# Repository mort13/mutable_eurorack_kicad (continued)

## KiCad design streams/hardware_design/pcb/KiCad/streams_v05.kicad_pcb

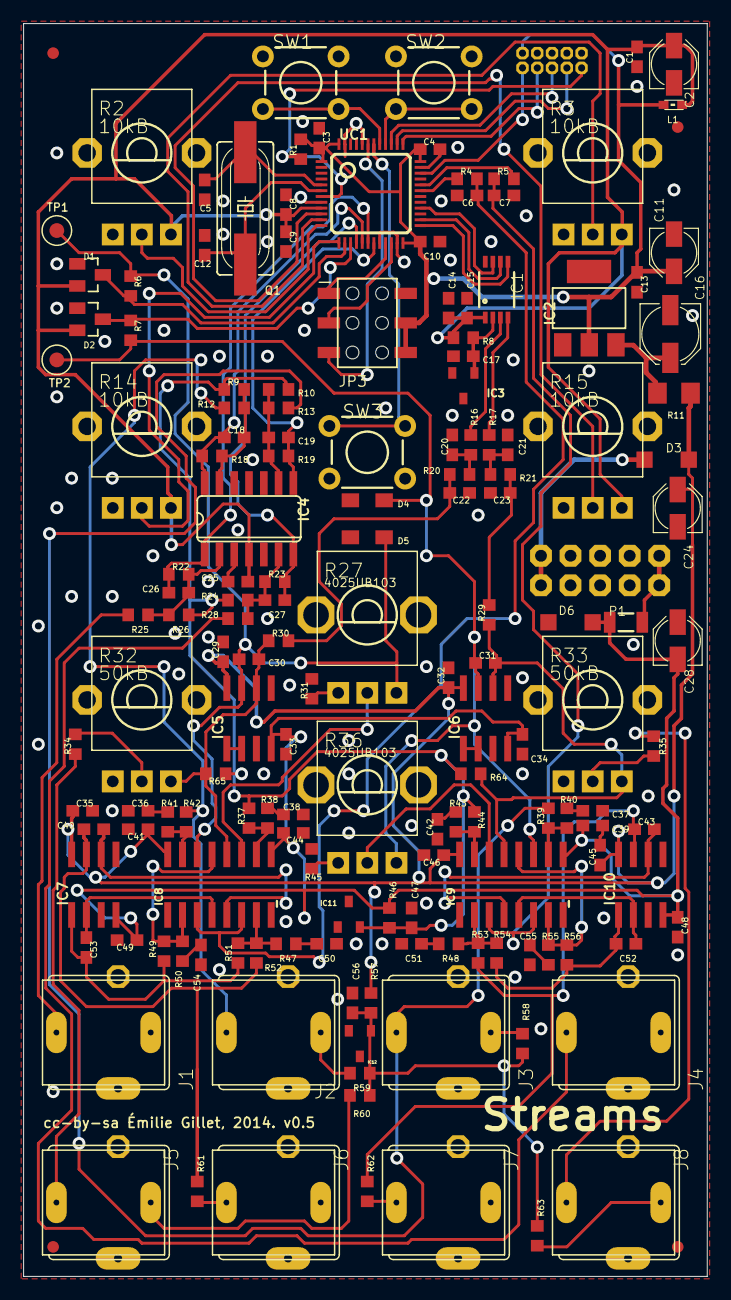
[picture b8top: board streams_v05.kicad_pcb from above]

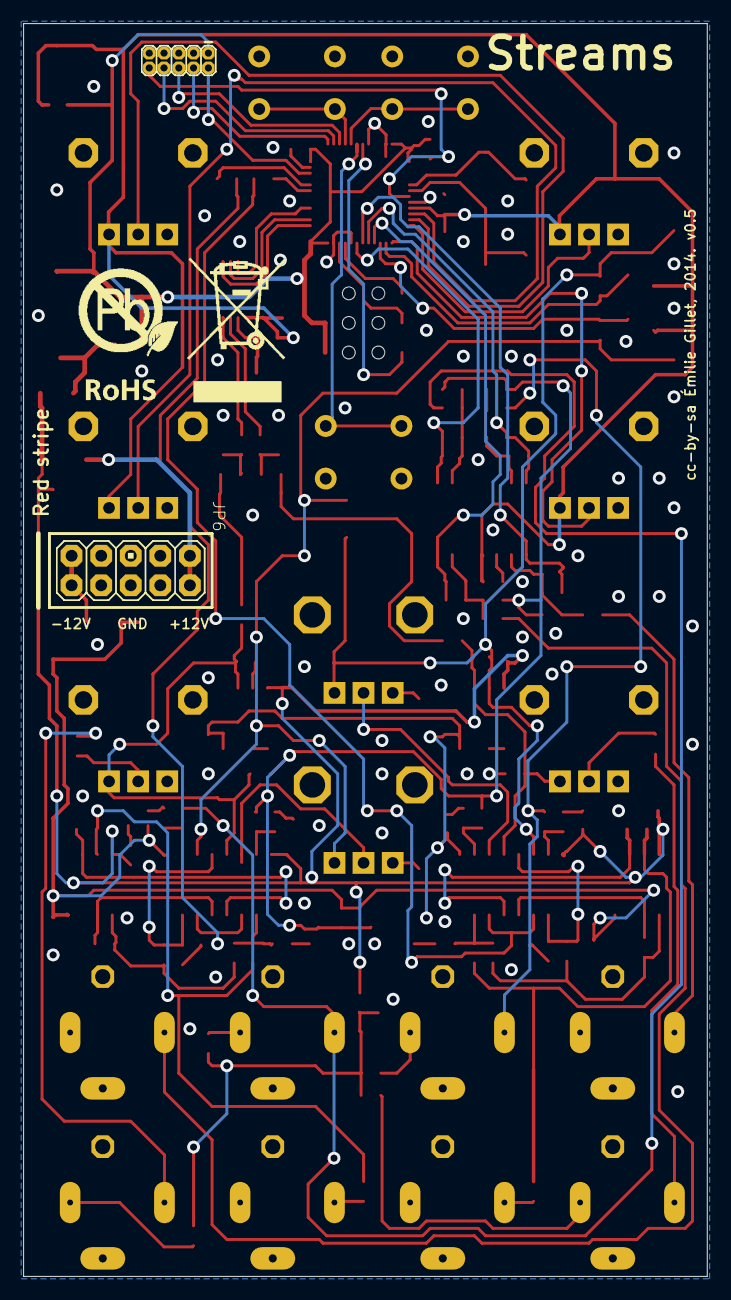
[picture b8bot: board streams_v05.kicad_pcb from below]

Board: 2 copper layers, 58.7 x 107.6 mm, 164 parts (3 on the bottom side), 99 nets.

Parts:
C1, C3, C4, C8, C10, C13, C14, C17, C25, C29, C32, C33, C34, C35, C39, C41, C44, C45, C46, C47, C48, C49, C56: 100n; C0603
C2, C24, C28: 10u; PANASONIC_B
C5, C12: 18p; C0603
C6, C7: 680n; C0603
C9, C15: 3.3u; C0603
C11: 22u; PANASONIC_B
C16: 22u; PANASONIC_C
C18, C19, C22, C23, C26, C27: 1.0n; C0603
C20, C21: 10n; C0603
C30, C31, C40, C43, C52, C53: 33p; C0603
C36, C37, C38, C42, C50, C51, C54, C55: 560p; C0603
D1, D2: BAT54S; SOT23
D3, D6: 1N5819HW; SOD123
D4, D5: 1N4148; SOD323-W
IC1: DAC8552; MSOP-8
IC2: LM1117-3.3; SOT223
IC3: LM4040B25; DBZ_R-PDSO-G3
IC4: MCP6004; SO14
IC5, IC6, IC7, IC10: TL072D; SO08
IC8, IC9: V2164SZ; SOIC16N
IC11, IC12: LM4040B10; DBZ_R-PDSO-G3
J1, J2, J3, J4, J5, J6, J7, J8: PJ301WQP; WQP_PJ_301BM_WIDER
JP1, JP2, JP4, JP5: FIDUCIAL1X2; FIDUCIAL-1X2
JP3: 2X3_BOTTOM
JP6: M05X2PTH; AVR_ICSP
JP7: M05X2MINIJTAG; 2X5-1.27
L1: 0603
P1: PTCSMD; PTC-1206
Q1: 8MHz; HC49UP
R1, R20, R21: 10k; R0603
R2, R3, R14, R15: 10kB; ALPS_POT_VERTICAL_PS
R4, R5: 1.2k; R0603
R6, R7, R16, R17, R46, R61, R62: 1.0k; R0603
R8, R57: 3.3k; R0603
R9, R10, R24, R26: 120k; R0603
R11: 4.7; R1206
R12, R13, R25, R28, R34, R35, R39, R42, R49, R51, R52, R53, R54, R56, R58, R59: 100k; R0603
R18, R19, R22, R23: 20k; R0603
R27, R36: 4025UB103; ALPS_POT_VERTICAL
R29, R30: 14k; R0603
R31, R38, R40, R41, R43, R45, R47, R48, R50, R55: 510; R0603
R32, R33: 50kB; ALPS_POT_VERTICAL_PS
R37, R44: 200k; R0603
R60, R63: 24.9k; R0603
R64, R65: 10M; R0603
SW1, SW2, SW3: TACTILE-PTH
TP1, TP2: TEST-POINT3X5; PAD.03X.05
U$1: ROHS_BIG
UC1: STM32F103CBT6; LQFP48

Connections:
+3V3: C3.1, C4.1, C10.1, C11.+, C13.1, IC2.2, JP3.4, JP3.6, JP7.1, L1.1, R1.2, UC1.1, UC1.24, UC1.36, UC1.48
+3V3_A: C1.1, C2.+, C8.1, C9.1, C14.1, C15.1, C25.1, D1.2, D2.2, IC1.1, IC4.4, L1.2, R2.P$1, R3.P$1, R8.1, R14.P$1, R15.P$1, UC1.9
ADC_AUX_1: C26.2, IC4.1, R22.2, UC1.18
ADC_AUX_2: C27.2, IC4.7, R23.2, UC1.16
ADC_CV_1: D1.3, R6.1, UC1.14
ADC_CV_2: D2.3, R7.1, UC1.15
ADC_IN_1: C18.2, IC4.14, R18.2, UC1.17
ADC_IN_2: C19.2, IC4.8, R19.2, UC1.19
AMOUNT_1: R14.P$2, UC1.13
AMOUNT_2: R15.P$2, UC1.10
AREF_2.5: C17.1, IC1.2, IC3.1, R8.2
AREF_+5: J2.SW, R59.1
AREF_+10: C56.1, IC12.1, R57.2, R58.2, R59.2, R60.2, R63.2
AREF_-10: C47.1, IC11.2, R9.1, R10.1, R24.1, R26.1, R37.1, R44.1, R46.2, R64.1, R65.1
BARGRAPH_CS: JP3.5, UC1.43
BARGRAPH_MOSI: JP3.1, UC1.21
BARGRAPH_SCK: JP3.3, UC1.22
DAC_1: C22.1, R20.2, R30.1
DAC_2: C23.1, R21.2, R29.1
DAC_MOSI: IC1.7, UC1.28
DAC_SCK: IC1.6, UC1.26
DAC_SS: IC1.5, UC1.25
FB_CURRENT1: IC8.10, R37.2, R38.2
FB_CURRENT2: IC8.15, R41.2, R42.2
FB_CURRENT3: IC9.10, R39.2, R40.2
FB_CURRENT4: IC9.15, R43.2, R44.2
GND: C1.2, C2.-, C3.2, C4.2, C5.1, C6.2, C7.2, C8.2, C9.2, C10.2, C11.-, C12.1, C13.2, C14.2, C15.2, C16.-, C17.2, C20.2, C21.2, C22.2, C23.2, C24.-, C25.2, C28.+, C29.2, C32.2, C33.1, C34.1, C35.2, C36.2, C37.2, C38.2, C39.1, C41.2, C42.2, C44.1, C45.2, C46.2, C47.2, C48.1, C49.1, C50.2, C51.2, C54.2, C55.2, C56.2, D1.1, D2.1, D4.A, D5.A, D6.C, IC1.8, IC2.1, IC3.2, IC4.3, IC4.5, IC4.10, IC4.11, IC4.12, IC5.3, IC5.5, IC6.3, IC6.5, IC7.3, IC7.5, IC8.8, IC9.8, IC10.3, IC10.5, IC11.1, IC12.2, J1.GND, J1.GND2, J2.GND, J2.GND2, J3.GND, J3.GND2, J4.GND, J4.GND2, J5.GND, J5.GND2, J6.GND, J6.GND2, J7.GND, J7.GND2, J8.GND, J8.GND2, JP3.2, JP6.3, JP6.4, JP6.5, JP6.6, JP6.7, JP6.8, JP7.3, JP7.5, JP7.9, R2.P$3, R3.P$3, R14.P$3, R15.P$3, R31.1, R32.P$3, R33.P$3, R45.1, SW1.1, SW1.2, SW2.1, SW2.2, SW3.1, SW3.2, UC1.8, UC1.20, UC1.23, UC1.35, UC1.44, UC1.47
IN_1: J2.TIP, R12.1, R42.1
IN_2: J3.TIP, R13.1, R39.1
JTCK: JP7.4, UC1.37
JTDI: JP7.8, UC1.38
JTDO: JP7.6, UC1.39
JTMS: JP7.2, UC1.34
unnamed: R27.P$3, R31.2
unnamed: C30.1, IC5.6, IC8.12, R30.2, R32.P$1, R65.2
unnamed: J8.SW, R63.1
unnamed: C37.1, R40.1
unnamed: C38.1, R38.1
unnamed: C5.2, Q1.2, UC1.5
unnamed: C12.2, Q1.1, UC1.6
unnamed: C31.1, IC6.6, IC9.13, R29.2, R33.P$1, R64.2
unnamed: C36.1, R41.1
unnamed: IC5.1, IC5.2
unnamed: J5.SW, R60.1
unnamed: J5.TIP, R34.1
unnamed: C43.1, IC9.4, IC10.6
unnamed: IC8.11, R27.P$2
unnamed: C43.2, IC10.7, R53.2, R62.1
unnamed: J7.TIP, R62.2
unnamed: R36.P$3, R45.2
unnamed: C42.1, R43.1
unnamed: C16.+, IC2.3, R11.2
unnamed: R32.P$2, R34.2
unnamed: R33.P$2, R35.2
unnamed: J8.TIP, R35.1
unnamed: C40.1, IC7.6, IC8.5
unnamed: C40.2, IC7.7, R52.2, R61.1
unnamed: IC6.1, IC6.2
unnamed: IC9.14, R36.P$2
unnamed: J3.SW, R58.1
unnamed: IC8.2, IC8.13, R49.1, R50.2
unnamed: D3.A, JP6.1, JP6.2
unnamed: JP6.9, JP6.10, P1.2
unnamed: J1.TIP, R25.1
unnamed: C27.1, IC4.6, R23.1, R24.2, R28.2
unnamed: J4.TIP, R28.1
unnamed: C18.1, IC4.13, R9.2, R12.2, R18.1
unnamed: C26.1, IC4.2, R22.1, R25.2, R26.2
unnamed: IC1.4, R17.1
unnamed: C19.1, IC4.9, R10.2, R13.2, R19.1
unnamed: IC1.3, R16.1
unnamed: C21.1, R17.2, R21.1
unnamed: C20.1, R16.2, R20.1
unnamed: IC9.7, IC9.12, R55.2, R56.1
unnamed: C52.1, IC9.5, IC10.2
unnamed: IC9.2, R48.2, R53.1, R54.2
unnamed: C52.2, IC10.1, R54.1, R56.2
unnamed: C53.1, IC7.2, IC8.4
unnamed: C55.1, R55.1
unnamed: C51.1, R48.1
unnamed: C53.2, IC7.1, R49.2, R51.1
unnamed: IC8.7, R47.2, R51.2, R52.1
unnamed: C54.1, R50.1
unnamed: C50.1, R47.1
unnamed: J6.TIP, R61.2
unnamed: R5.1, UC1.32
unnamed: R4.1, UC1.31
PWM_CUTOFF_1: C6.1, IC8.3, IC8.6, R4.2
PWM_CUTOFF_2: C7.1, IC9.3, IC9.6, R5.2
RESET: JP7.10, R1.1, UC1.7
SHAPE_1: R2.P$2, UC1.12
SHAPE_2: R3.P$2, UC1.11
SW_METER: SW3.3, SW3.4, UC1.42
SW_MODE_1: SW1.3, SW1.4, UC1.41
SW_MODE_2: SW2.3, SW2.4, UC1.40
VCA_CONTROL_1: C30.2, D5.C, IC5.7, IC8.14, R6.2, R27.P$1, TP1.P$1
VCA_CONTROL_2: C31.2, D4.C, IC6.7, IC9.11, R7.2, R36.P$1, TP2.P$1
VCC: C24.+, C29.1, C32.1, C35.1, C41.1, C45.1, C46.1, D3.C, IC5.8, IC6.8, IC7.8, IC8.16, IC9.16, IC10.8, R11.1, R57.1
VEE: C28.-, C33.2, C34.2, C39.2, C44.2, C48.2, C49.2, D6.A, IC5.4, IC6.4, IC7.4, IC8.9, IC9.9, IC10.4, P1.1, R46.1

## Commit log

2020-03-23 Updated README for fork; XML conversions
2020-03-23 add KiCad stuff
2020-03-23 KiCad ears
2020-03-23 KiCad
2020-09-01 Some KiCad imports
2020-09-16 Clouds KiCad import
2020-10-09 Veils KiCad import
2022-06-13 elements KiCad import
2022-06-13 KiCad imports
2022-07-03 Can no longer supply XML versions
2023-01-11 clouds import etc.
2023-05-24 Re-imports
2023-07-31 Redo Ears
2023-07-31 .gitignore update, add lib tables and caches
